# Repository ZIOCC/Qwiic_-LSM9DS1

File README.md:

# Zio Qwiic 9DOF IMU LSM9DS1

> This product can be available for purchase [here](https://www.smart-prototyping.com/Zio-9DOF-IMU-LSM9DS1.html).

#### Description

The Zio 9DOF IMU LSM9DS1 is an all-around good pick for any orientation needs that don’t require on-sensor fusion. Like other 9-Degree-of-Freedom (9DOF) Inertial Measurement Units (IMU), it combines a 3-axis accelerometer, 3-axis gyroscope, 3-axis magnetometer in one tiny IC. Those sensors measure linear acceleration, angular velocity, and magnetic field strength, respectively. Additionally, there is an on-die temperature sensor that can be used to offset the effects of temperature on the other three sensor types.

With the right code to interpret all of this data, you can get a an excellent idea of the sensor package’s orientation in space, and the amplitude of the forces affecting it, even as it moves. You can use this to knowledge to stabilize a drone, a camera gimbal, or an electric unicycle. Or you can use it to capture and analyze the movements of a human or, for that matter, anything else that moves.

The sensor will output 10 different pieces of raw data: acceleration in x/y/z, angular rotation speed in x/y/z, magnetic force in x/y/z, and temperature. Combined, this information can be used to produce a clear image of an object’s movement and orientation. 

We’ve brought this solid little chip into the [Qwiic ecosystem](https://www.smart-prototyping.com/qwiic.html) by mounting it on a breakout board equipped with two Qwiic connectors. It can easily and quickly be daisy-chained to any other I2C boards in the system. We’ve opted to break out all of the pins for this sensor, making this a good general-purpose IMU breakout, and be used with SPI if you need a faster interface to your MCU.

There is a wide-variety of applications that this board can be used in such as AR, VR, robotic SLAM navigation, gaming, fitness tracking, context awareness (identification of the scenario in which a user is currently engaged), model rocket telemetry and more.

> Note: As with all of the Version 1.0 Zio Qwiic boards, this board has been produced with the I2C pull-ups disconnected by default. If there's a significant length of wire between this board and your MCU, you'll need to solder closed the solder jumpers (labeled SDA, 3v3 and SCL) to connect the pull-up resistors to VCC.

#### Specification

* Linear Acceleration Range: ±2/±4/±8/±16 g
* Magnetic Range: ±4/±8/±12/±16 gauss
* Angular Rate Range: ±245/±500/±2000 dps
* Data Output Resolution: 16-bit
* Communication Protocols: I2C, SPI
* IC: LSM9DS1
* I2C address:  Accelerometer and gyroscope: 0x6B, Magnetic: 0x1E
* Dimensions: 36.6x 20.7mm
* Weight: 1.8g (0.067oz)

#### Links

* [LSM9DS1 Datasheet](https://www.smart-prototyping.com/image/data/NOA-RnD/101893%209DOF%20IMU%20LSM9DS1/LSM9DS1_datasheet.pdf)
* [SparkFun LSM9DS1 Arduino Library](https://github.com/sparkfun/SparkFun_LSM9DS1_Arduino_Library)
* [Eagle files](https://github.com/ZIOCC/Qwiic_LSM9DS1)

> ###### About Zio
> Zio is a new line of open sourced, compact, and grid layout boards, fully integrated for Arduino and Qwiic ecosystem. Designed ideally for wearables, robotics, small-space limitations or other on the go projects. Check out other awesome Zio products [here](https://www.smart-prototyping.com/Zio).

> All Zio products are released under the [Creative Commons Attribution, Share-Alike License](https://creativecommons.org/licenses/by-sa/4.0/), and in accordance with the principles of the [Open Source Hardware Association's OSHW Statement of Principles 1.0 and OSHW Definition 1.0](https://www.oshwa.org/definition/).

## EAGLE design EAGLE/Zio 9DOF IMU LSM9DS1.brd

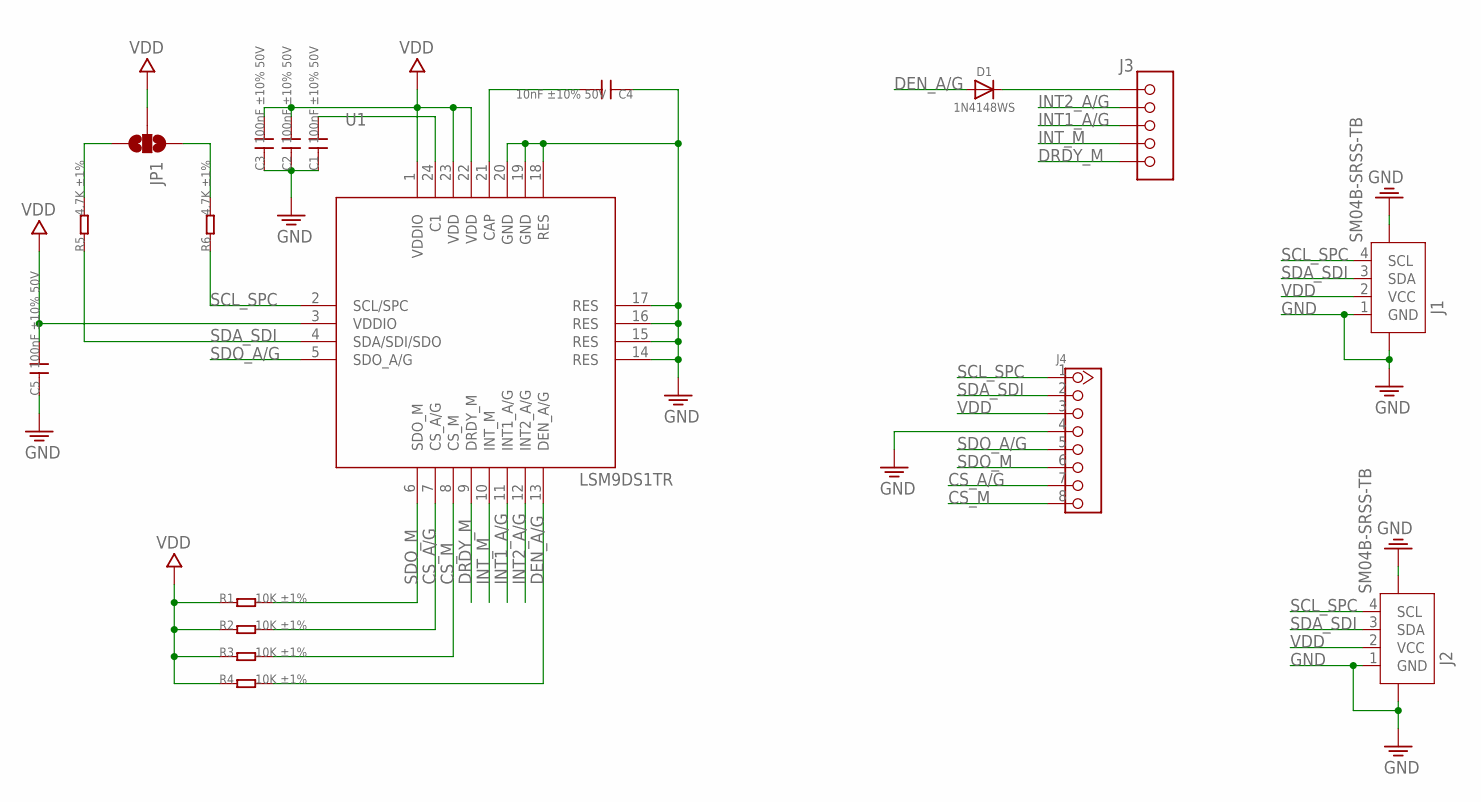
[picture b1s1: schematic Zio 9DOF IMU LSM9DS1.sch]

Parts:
C1, C2, C3, C5: 100nF ±10% 50V; 0402
C4: 10nF ±10% 50V; 0402
D1: 1N4148WS; SOD-323
J1, J2: SM04B-SRSS-TB; JST-SH-4P
J3: HEADER-5P-2.54; 5P-2.54
J4: HEADER-8P-2.54; 8P-2.54
JP1: JUMPER-SMT_3_2-NC_PASTE_NOCREM; SMT-JUMPER_3_2-NC_PASTE_SILK_NOCREM
R1, R2, R3, R4: 10K ±1%; 0402
R5, R6: 4.7K ±1%; 0402
U1: LSM9DS1TR; LGA24

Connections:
CS_A/G: J4.7, R2.2, U1.7 (CS_A/G)
CS_M: J4.8, R3.2, U1.8 (CS_M)
DEN_A/G: D1.A, R4.2, U1.13 (DEN_A/G)
DRDY_M: J3.5, U1.9 (DRDY_M)
GND: C1.1, C2.1, C3.1, C4.1, C5.1, J1.1 (GND), J1.NC1 (5), J1.NC2 (6), J2.1 (GND), J2.NC1 (5), J2.NC2 (6), J4.4, U1.14 (RES), U1.15 (RES), U1.16 (RES), U1.17 (RES), U1.18 (RES), U1.19 (GND), U1.20 (GND)
INT1_A/G: J3.3, U1.11 (INT1_A/G)
INT2_A/G: J3.2, U1.12 (INT2_A/G)
INT_M: J3.4, U1.10 (INT_M)
unnamed: C1.2, U1.24 (C1)
unnamed: JP1.3, R5.2
unnamed: JP1.1, R6.2
unnamed: C4.2, U1.21 (CAP)
unnamed: D1.C, J3.1
SCL_SPC: J1.4 (SCL), J2.4 (SCL), J4.1, R6.1, U1.2 (SCL/SPC)
SDA_SDI: J1.3 (SDA), J2.3 (SDA), J4.2, R5.1, U1.4 (SDA/SDI/SDO)
SDO_A/G: J4.5, U1.5 (SDO_A/G)
SDO_M: J4.6, R1.2, U1.6 (SDO_M)
VDD: C2.2, C3.2, C5.2, J1.2 (VCC), J2.2 (VCC), J4.3, JP1.2, R1.1, R2.1, R3.1, R4.1, U1.1 (VDDIO), U1.3 (VDDIO), U1.22 (VDD), U1.23 (VDD)

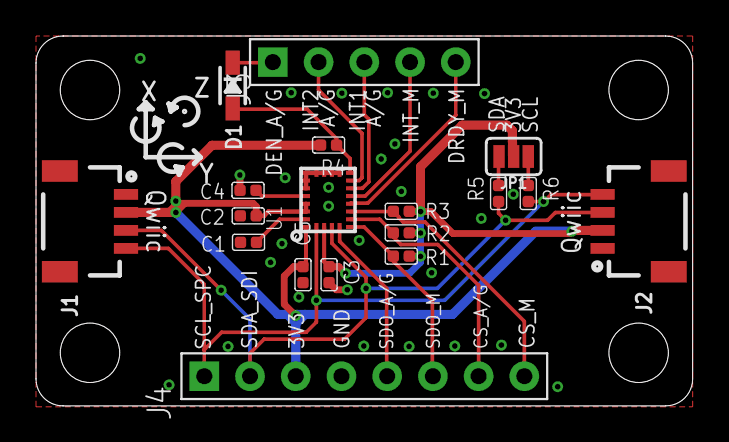
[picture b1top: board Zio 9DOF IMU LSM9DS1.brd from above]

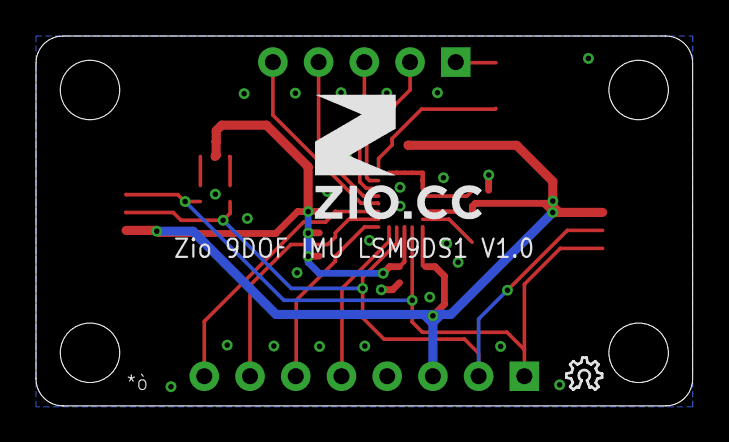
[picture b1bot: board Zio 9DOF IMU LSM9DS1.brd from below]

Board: 2 copper layers, 36.5 x 20.5 mm, 24 parts (2 on the bottom side), 18 nets.

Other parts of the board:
LOGO1: LOGO-OSHW-6MILX0070-NT; OSHW_6X70_NOTEXT
U$2, U$11, U$12, U$13: STAND-OFF
U$18: 7MM

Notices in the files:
parts and their libraries:
microbuilder: This work is placed in the public domain, and may be freely used for commercial and non-commercial work with the following conditions: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
SparkFun-Hardware: Licensing: Creative Commons ShareAlike 4.0 International - https://creativecommons.org/licenses/by-sa/4.0
